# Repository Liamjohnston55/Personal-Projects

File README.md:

# Personal Projects

This repository contains personal electrical and software engineering projects focused on embedded systems, PCB design, and hardware integration.

Most of these projects are built from the ground up, including:
- Firmware development (ESP32, Arduino framework)
- Custom PCB schematic and layout in KiCad
- Hardware debugging and system integration
- 3D printed mechanical design
- Power management and battery systems

The goal of these projects is practical system implementation — taking a concept from idea to working hardware.

---

## Projects

### ESP32 MP3 Jukebox
Custom embedded audio system built around an ESP32 with a fully designed PCB, firmware, and enclosure.

Includes:
- ESP32 firmware
- Custom KiCad schematic and PCB layout
- Gerber manufacturing files
- Mechanical STL files
- System documentation

Project folder: `MP3 Jute Box/`

---

More projects will be added as they are completed.

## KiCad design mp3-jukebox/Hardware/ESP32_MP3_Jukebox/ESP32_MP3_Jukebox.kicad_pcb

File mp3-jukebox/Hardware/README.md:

# Hardware Design – ESP32 MP3 Jukebox

This folder contains the complete KiCad project files for the custom
ESP32-based MP3 Jukebox PCB.

## Overview

The PCB integrates:

- ESP32-WROOM-32 Dev Board
- DFPlayer Mini (DFR0299)
- SSD1306 128x64 I2C OLED
- PAM8403 Audio Amplifier
- Pushbutton GPIO inputs
- Analog volume control (ADC)
- 5V USB-C power input

The design is a 2-layer PCB with dedicated power and signal routing.

---

## Files Included

- `.kicad_pro` – KiCad project file  
- `.kicad_sch` – Complete schematic  
- `.kicad_pcb` – PCB layout  
- `Gerbers/` – Manufacturing-ready Gerber files  
- `Libraries/` – External symbol and footprint files used  

---

## Manufacturing

The Gerber files were generated using KiCad 9.0.

To fabricate:

1. Upload the `Gerbers/` folder as a zip file to:
   - JLCPCB
   - PCBWay
   - Any standard PCB manufacturer

2. Standard settings:
   - 2-layer board
   - 1.6mm thickness
   - HASL finish
   - 1oz copper

---

## Design Notes

- Separate analog and digital routing where possible.
- Audio lines kept short to minimize noise.
- Power rails routed with wider traces.
- Mounting holes included for enclosure integration.

---

## External Libraries Used

- DFPlayer Mini (DFR0299) – SnapEDA  
- ESP32 DevKit – Espressif KiCad Libraries  
- SSD1306 OLED – KiCad-SSD1306-128x64  
- PAM8403 Amplifier – pam8403-module-kicad-lib  

See main README for full repository links.

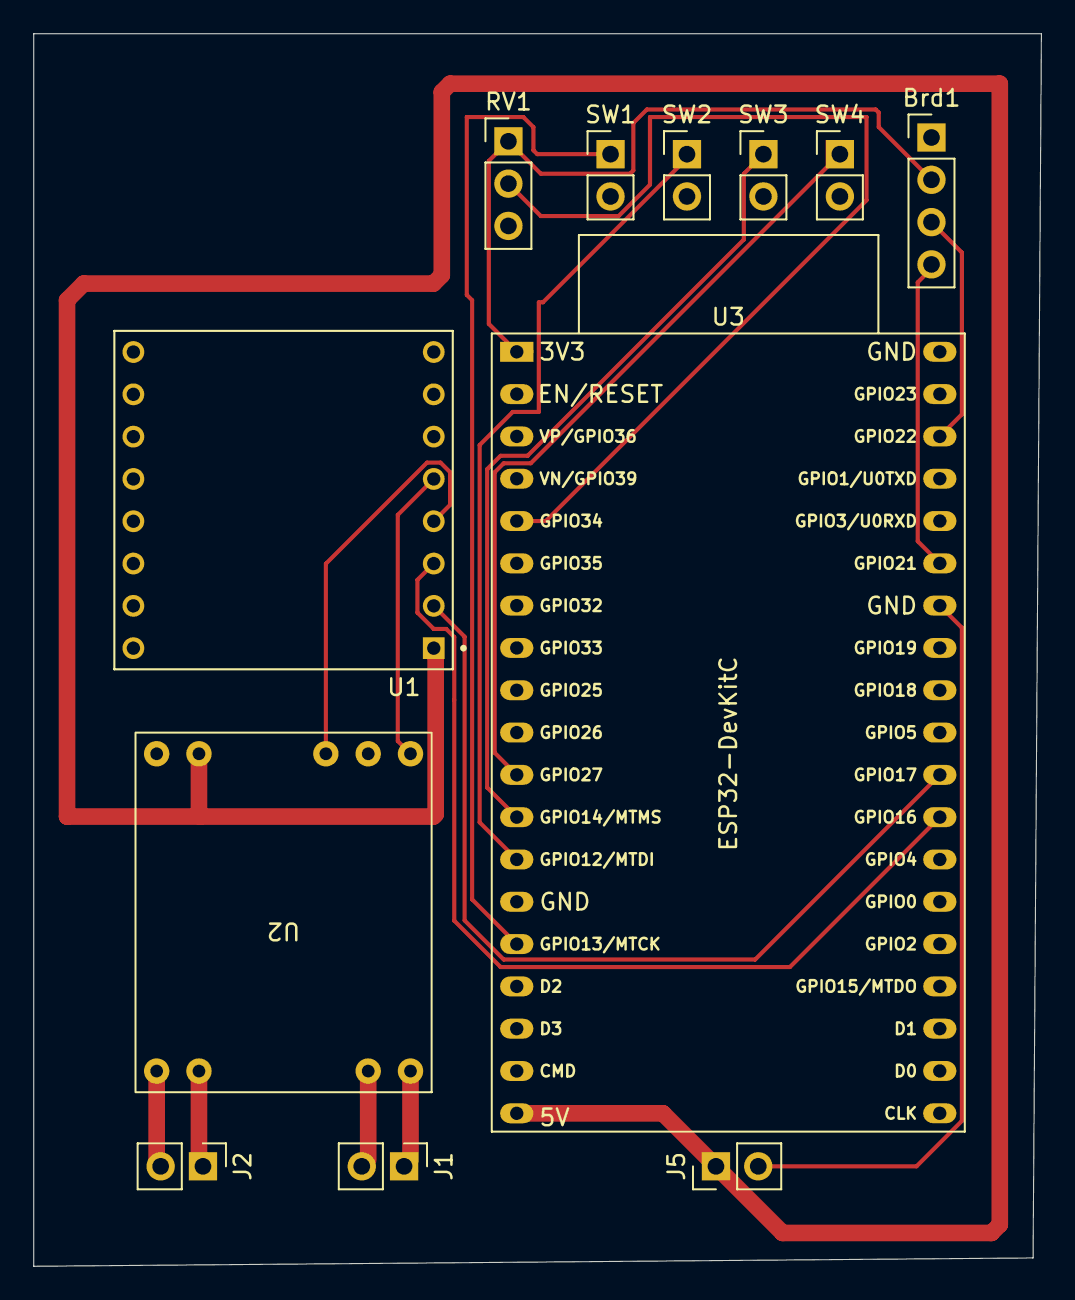
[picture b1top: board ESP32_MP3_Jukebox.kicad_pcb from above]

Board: 2 copper layers, 60.5 x 74.0 mm, 12 parts (0 on the bottom side), 18 nets.

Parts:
Brd1: SSD1306; PinHeader_1x04_P2.54mm_Vertical
J1: Speaker 1; PinHeader_1x02_P2.54mm_Vertical
J2: Speaker 2; PinHeader_1x02_P2.54mm_Vertical
J5: USB-C Board; PinHeader_1x02_P2.54mm_Vertical
RV1: R_Potentiometer; PinHeader_1x03_P2.54mm_Vertical
SW1: BTN_UP; PinHeader_1x02_P2.54mm_Vertical
SW2: BTN_DOWN; PinHeader_1x02_P2.54mm_Vertical
SW3: BTN_PLAY; PinHeader_1x02_P2.54mm_Vertical
SW4: BTN_BACK; PinHeader_1x02_P2.54mm_Vertical
U1: DFPlayer; MODULE_DFR0299
U2: pam8403
U3: ESP32-DevKitC

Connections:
+3.3V: Brd1.2 (VCC), RV1.1, U3.1 (3V3)
+5V: J5.1, U1.1 (VCC), U2.4 (vin), U3.19 (5V)
GND: Brd1.1 (GND), J5.2, RV1.3, SW1.2, SW2.2, SW3.2, SW4.2, U1.7 (GND), U1.10 (GND), U2.2 (T), U2.5 (gnd), U3.14 (GND), U3.32 (GND), U3.38 (GND)
unnamed: Brd1.3 (SCL), U3.36 (GPIO22)
unnamed: Brd1.4 (SDA), U3.33 (GPIO21)
unnamed: J1.1, U2.9 (L-)
unnamed: J1.2, U2.8 (L+)
unnamed: J2.1, U2.7 (R+)
unnamed: J2.2, U2.6 (R-)
unnamed: U1.5 (DAC_L), U2.1 (L)
unnamed: U1.4 (DAC_R), U2.3 (R)
unnamed: U1.2 (RX), U3.28 (GPIO17)
unnamed: U1.3 (TX), U3.27 (GPIO16)
unnamed: SW4.1, U3.11 (ADC2_CH7/GPIO27)
unnamed: SW1.1, U3.15 (MTCK/GPIO13/ADC2_CH4)
unnamed: SW2.1, U3.13 (MTDI/GPIO12/ADC2_CH5)
unnamed: SW3.1, U3.12 (MTMS/GPIO14/ADC2_CH6)
unnamed: RV1.2, U3.5 (VDET_1/GPIO34/ADC1_CH6)

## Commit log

2026-03-16 Initial commit: add ESP32 MP3 Jukebox project
    Add complete ESP32-based MP3 Jukebox project including firmware,
    hardware design files, and documentation.
    This commit includes:
    - ESP32 firmware implementing menu navigation, OLED display output,
    DFPlayer Mini communication, and playback control
    - KiCad schematic and PCB layout for the custom ESP32 MP3 Jukebox board
2026-03-17 Renamed project files for consistency and improved organization
